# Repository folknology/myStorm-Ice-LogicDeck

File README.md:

# Ice LogicDeck 
The very first myStorm [Tile](https://github.com/folknology/Tiles) based logic deck, designed around the combination of a powerful STM32 F7 microcontroller fused with a fully configurable Lattice Ice40Hx FPGA.
This forms a modular, heterogeneous embedded development system, it is very much WIP. We will add more documentation soon, you can follow the [live](https://www.twitch.tv/folknology) streaming [narrative](https://www.youtube.com/playlist?list=PLXS9jyX9czzqn4HU2mEmoEFxpgIv1Dvy7) as we develop it, you can follow the evolving [documentation](https://folknology.github.io/myStorm-Ice-LogicDeck/).

#### The 'Deck' based solution is formed by combining multiple [Tiles](https://github.com/folknology/Tiles) and the Ice Logic board carrier

#### Together these form an Ice LogicDeck solution

### Hardware, development, tooling and software
- [Hardware sources](https://github.com/folknology/myStorm-Ice-LogicDeck/tree/main/Hardware)
- [Firmware sources](https://github.com/folknology/BlackCrab)
- [Examples & board support](https://github.com/folknology/myStorm-Ice-LogicDeck/tree/main/HDL)
- [FPGA HDL/Synthesis, PNR, simulation and formal - Yosys OSS cad suite](https://github.com/YosysHQ/oss-cad-suite-build)

### Further information
- [Tiles](https://github.com/folknology/Tiles)
- [Documentation](https://folknology.github.io/myStorm-Ice-LogicDeck/)
- [Discuss LogicDecks on Discord](https://discord.gg/RCGcgbQNZK)

### OpenSource Design

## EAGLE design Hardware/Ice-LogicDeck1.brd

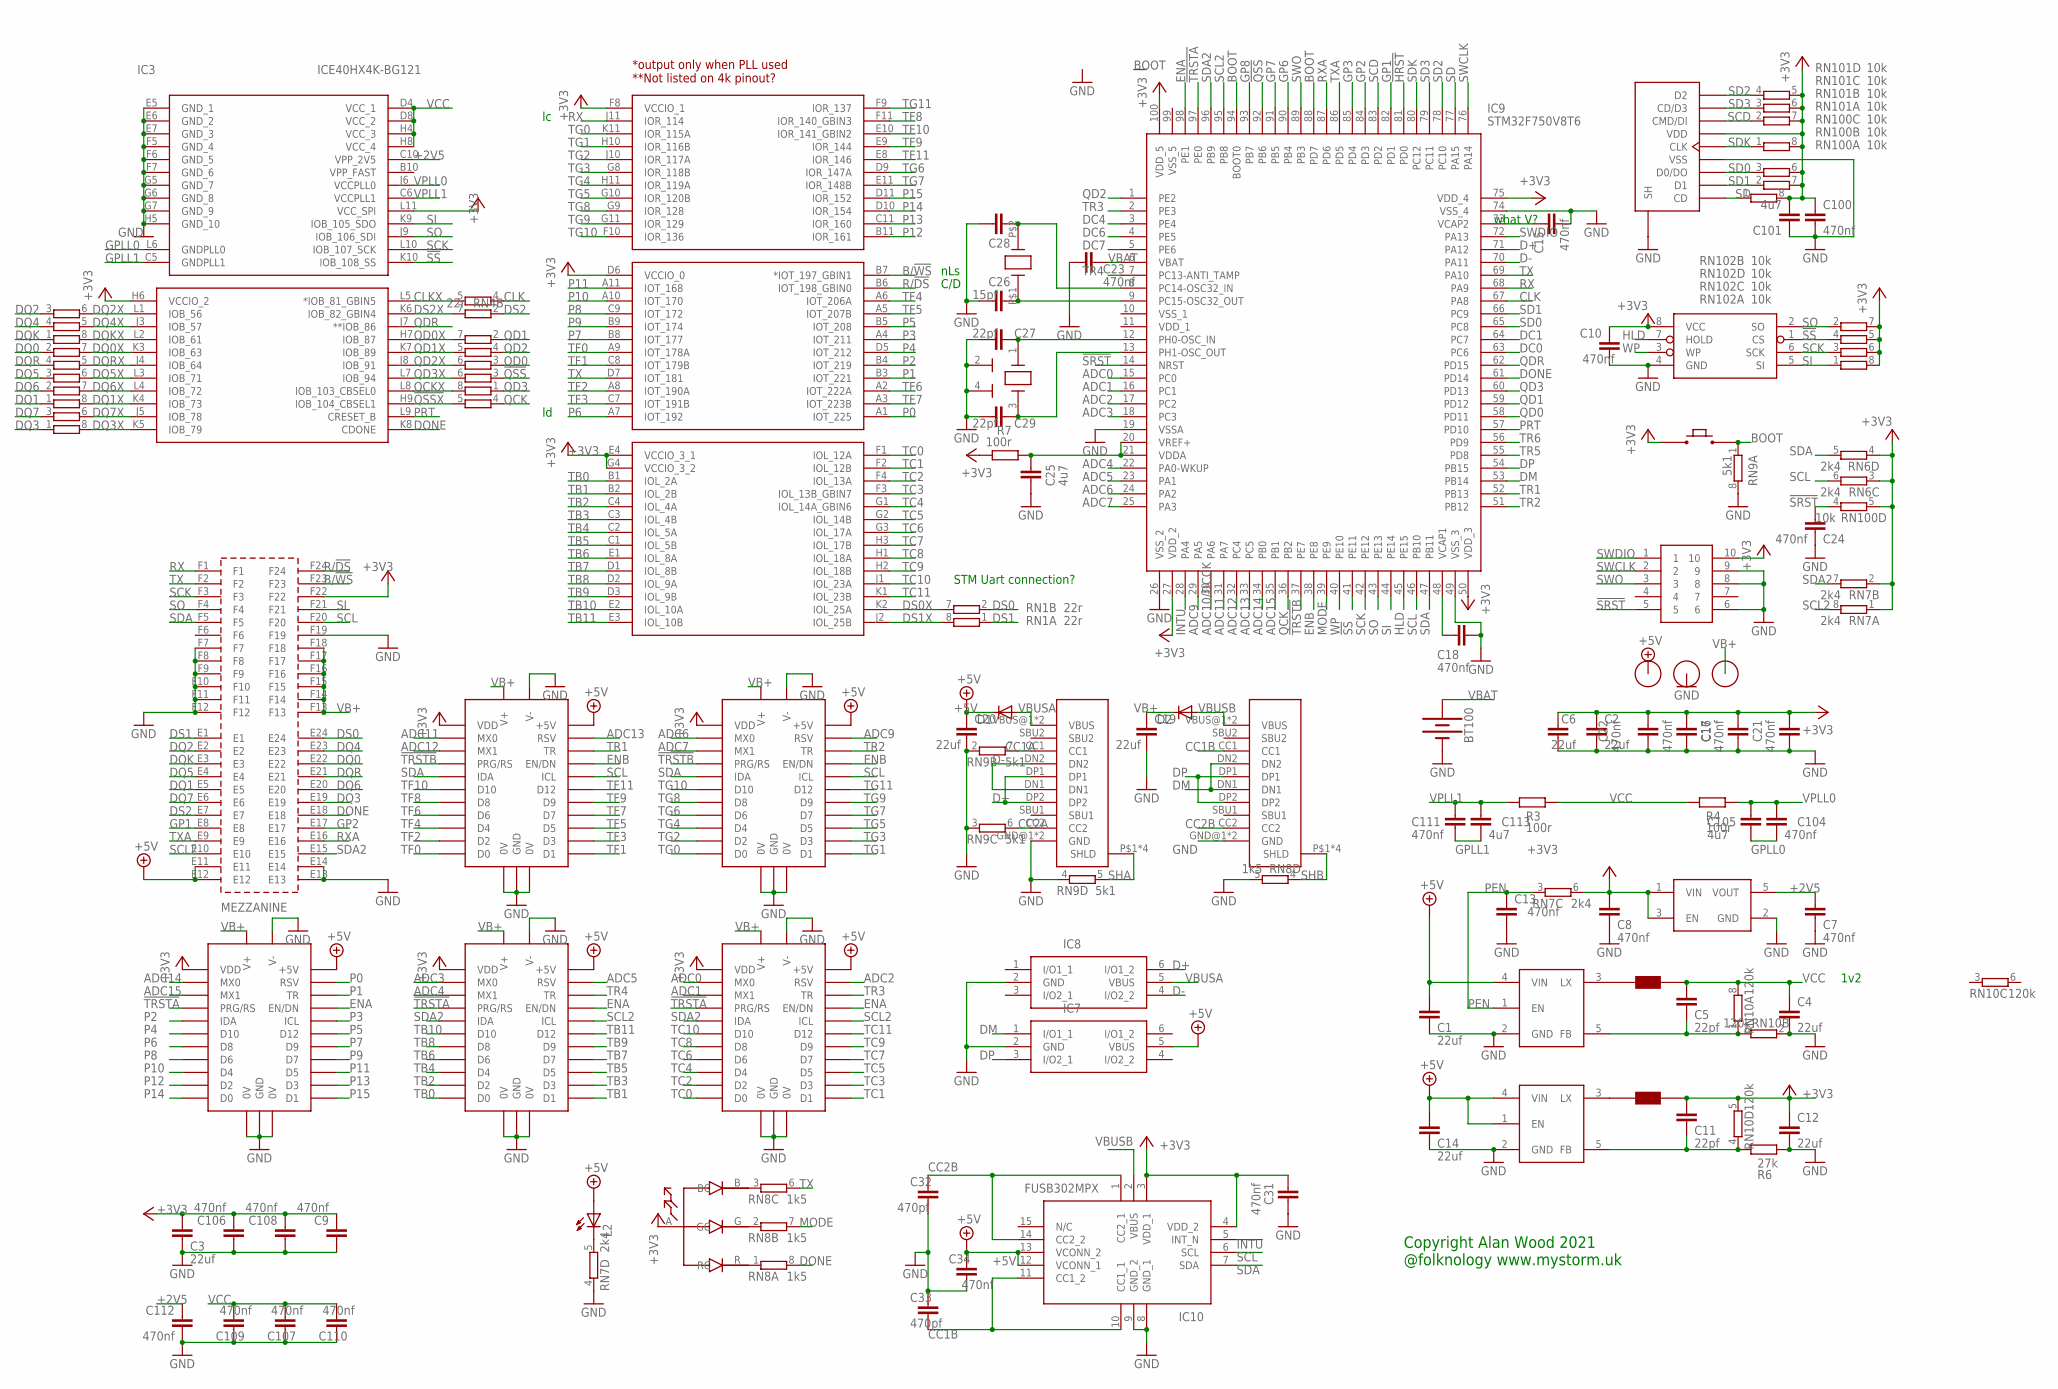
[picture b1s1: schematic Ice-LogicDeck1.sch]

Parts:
BT100: BATTERY-20MM_SMD; BATTCON_20MM
C1, C2, C3, C4, C6, C12, C14, C19, C20: 22uf; C0603
C5, C11, C27, C29: 22pf; C0402
C7, C8, C9, C10, C13, C15, C16, C17, C18, C21, C22, C23, C24, C31, C34, C100, C104, C106, C107, C108, C109, C110, C111, C112: 470nf; C0402
C25, C101, C105, C113: 4u7; C0402
C26, C28: 15pf; C0402
C32, C33: 470pf; C0402
CN1, CN2: USB-C-16; USB-C
CN3: 2X5-HEADER; 1.27-2X5-HEADER
D1, D2: DIODE-SOD123; SOD123
DFU: 4X3-RA-BUTTON
H1, H3, H4: HOLE2.5MM-LARGE; 2M5-LARGE
I1, I2: NRS4018; NRC4018
IC1, IC5: AP3429/A; TSOP-5/SOT23-5
IC2: NCP114; TSOP-5/SOT23-5
IC3: ICE40HX4K-BG121; BGA121C80P11X11_900X900X110
IC4: AT25SDF041A; SOIC-8-NARROW
IC7, IC8: USBLC6-2SC6; SOT95P280X145-6N
IC9: STM32F750V8T6; QFP50P1600X1600X160-100N
IC10: FUSB302MPX; QFN50P250X250X80-15N
L1: RGB_LED; RGB_LED_IMM
L2: LEDCHIPLED_0805; CHIPLED_0805
MEZZANINE: HYPER-TILECARRIER; HYPER-TILE
R3, R4, R7: 100r; R0402
R6: 27k; R0402
RN1, RN2, RN3, RN4, RN5: 22r; EXB38V
RN6, RN7: 2k4; EXB38V
RN8: 1k5; EXB38V
RN9: 5k1; EXB38V
RN10: 120k; EXB38V
RN100, RN101, RN102: 10k; EXB38V
SD100: TF-15X15; SDCARD
TILE1, TILE2, TILE3, TILE4, TILE5: UTILE_LPCARRIER_SMD_MALE_1.27; UTILE_LP
Y1: 12MZ; CRYSTAL-3.2X2.5
Y2: FC-135; FC135

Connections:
!HRST: IC9.81 (PD0)
!QSS: IC9.92 (PB6), RN4.3 (1)
!QSSX: IC3.H9 (IOB_104_CBSEL1), RN5.5 (2)
!SRST: C24.2, CN3.5, IC9.14 (NRST), RN100.4 (1)
!SS: IC3.K10 (IOB_108_SS), IC4.1 (CS), IC9.41 (PE11), RN102.4 (1)
!TRSTA: IC9.97 (PE0), TILE1.P$15 (PRG/RS), TILE2.P$15 (PRG/RS), TILE4.P$15 (PRG/RS)
!TRSTB: IC9.37 (PE7), TILE3.P$15 (PRG/RS), TILE5.P$15 (PRG/RS)
+2V5: C7.2, C112.1, IC2.5 (VOUT), IC3.C10 (VPP_2V5)
+3V3: C2.1, C3.2, C6.2, C8.2, C9.1, C10.1, C11.2, C12.1, C16.2, C17.2, C21.2, C22.2, C31.2, C100.1, C101.2, C106.1, C108.1, CN3.10, DFU.P$1, I2.P$2, IC2.1 (VIN), IC2.3 (EN), IC3.D6 (VCCIO_0), IC3.E4 (VCCIO_3_1), IC3.F8 (VCCIO_1), IC3.G4 (VCCIO_3_2), IC3.H6 (VCCIO_2), IC3.L11 (VCC_SPI), IC4.8 (VCC), IC9.27 (VDD_2), IC9.50 (VDD_3), IC9.75 (VDD_4), IC9.100 (VDD_5), IC10.3 (VDD_1), IC10.4 (VDD_2), L1.A (ANODE), MEZZANINE.F22, R7.2, RN6.3 (1), RN6.4 (1), RN7.1, RN7.2 (1), RN7.6 (2), RN10.5 (2), RN100.5 (2), RN100.6 (2), RN100.7 (2), RN100.8 (2), RN101.5 (2), RN101.6 (2), RN101.7 (2), RN101.8 (2), RN102.5 (2), RN102.6 (2), RN102.7 (2), RN102.8 (2), SD100.P$6 (VDD), TILE1.P$18 (VDD), TILE2.P$18 (VDD), TILE3.P$18 (VDD), TILE4.P$18 (VDD), TILE5.P$18 (VDD)
+5V: C1.2, C14.2, C20.1, C34.2, D1.C, H1.P$1, IC1.4 (VIN), IC5.1 (EN), IC5.4 (VIN), IC7.5 (VBUS), IC10.12 (VCONN_1), IC10.13 (VCONN_2), L2.A, MEZZANINE.E11, MEZZANINE.E12, TILE1.P$43 (+5V), TILE2.P$43 (+5V), TILE3.P$43 (+5V), TILE4.P$43 (+5V), TILE5.P$43 (+5V)
ADC0: IC9.15 (PC0), TILE4.P$17 (MX0)
ADC1: IC9.16 (PC1), TILE4.P$16 (MX1)
ADC2: IC9.17 (PC2), TILE4.P$42 (RSV)
ADC3: IC9.18 (PC3), TILE1.P$17 (MX0)
ADC4: IC9.22 (PA0-WKUP), TILE1.P$16 (MX1)
ADC5: IC9.23 (PA1), TILE1.P$42 (RSV)
ADC6: IC9.24 (PA2), TILE5.P$17 (MX0)
ADC7: IC9.25 (PA3), TILE5.P$16 (MX1)
ADC9: IC9.29 (PA5), TILE5.P$42 (RSV)
ADC10/DCCK: IC9.30 (PA6)
ADC11: IC9.31 (PA7), TILE3.P$17 (MX0)
ADC12: IC9.32 (PC4), TILE3.P$16 (MX1)
ADC13: IC9.33 (PC5), TILE3.P$42 (RSV)
ADC14: IC9.34 (PB0), TILE2.P$17 (MX0)
ADC15: IC9.35 (PB1), TILE2.P$16 (MX1)
B/!WS: IC3.B7 (*IOT_197_GBIN1), MEZZANINE.F23
BOOT: DFU.P$2, IC9.88 (PD7), IC9.94 (BOOT0), RN9.1
CC1A: CN1.CC1, RN9.7 (2)
CC1B: C33.1, CN2.CC1, IC10.10 (CC1_1), IC10.11 (CC1_2)
CC2A: CN1.CC2, RN9.6 (2)
CC2B: C32.2, CN2.CC2, IC10.1 (CC2_1), IC10.14 (CC2_2)
CLK: IC9.67 (PA8), RN3.4 (1)
CLKX: IC3.L5 (*IOB_81_GBIN5), RN3.5 (2)
D+: CN1.DP1, CN1.DP2, IC8.6 (I/O1_2), IC9.71 (PA12)
D-: CN1.DN1, CN1.DN2, IC8.4 (I/O2_2), IC9.70 (PA11)
DC0: IC9.63 (PC6)
DC1: IC9.64 (PC7)
DC4: IC9.3 (PE4)
DC6: IC9.4 (PE5)
DC7: IC9.5 (PE6)
DM: CN2.DN1, CN2.DN2, IC7.1 (I/O1_1), IC9.53 (PB14)
DONE: IC3.K8 (CDONE), IC9.61 (PD14), MEZZANINE.E18, RN8.8 (2)
DP: CN2.DP1, CN2.DP2, IC7.3 (I/O2_1), IC9.54 (PB15)
DQ0: MEZZANINE.E22, RN2.2 (1)
DQ0X: IC3.K3 (IOB_63), RN2.7 (2)
DQ1: MEZZANINE.E5, RN3.1
DQ1X: IC3.K4 (IOB_73), RN3.8 (2)
DQ2: MEZZANINE.E2, RN1.3 (1)
DQ2X: IC3.L1 (IOB_56), RN1.6 (2)
DQ3: MEZZANINE.E19, RN4.1
DQ3X: IC3.K5 (IOB_79), RN4.8 (2)
DQ4: MEZZANINE.E23, RN1.4 (1)
DQ4X: IC3.J3 (IOB_57), RN1.5 (2)
DQ5: MEZZANINE.E4, RN2.3 (1)
DQ5X: IC3.L3 (IOB_71), RN2.6 (2)
DQ6: MEZZANINE.E20, RN3.2 (1)
DQ6X: IC3.L4 (IOB_72), RN3.7 (2)
DQ7: MEZZANINE.E6, RN3.3 (1)
DQ7X: IC3.J5 (IOB_78), RN3.6 (2)
DQK: MEZZANINE.E3, RN2.1
DQKX: IC3.L2 (IOB_61), RN2.8 (2)
DQR: MEZZANINE.E21, RN2.4 (1)
DQRX: IC3.J4 (IOB_64), RN2.5 (2)
DS0: MEZZANINE.E24, RN1.2 (1)
DS0X: IC3.K2 (IOL_25A), RN1.7 (2)
DS1: MEZZANINE.E1, RN1.1
DS1X: IC3.J2 (IOL_25B), RN1.8 (2)
DS2: MEZZANINE.E7, RN4.2 (1)
DS2X: IC3.K6 (IOB_82_GBIN4), RN4.7 (2)
ENA: IC9.98 (PE1), TILE1.P$40 (EN/DN), TILE2.P$40 (EN/DN), TILE4.P$40 (EN/DN)
ENB: IC9.38 (PE8), TILE3.P$40 (EN/DN), TILE5.P$40 (EN/DN)
GND: BT100.2 (-), C1.1, C2.2, C3.1, C4.2, C6.1, C7.1, C8.1, C9.2, C10.2, C12.2, C13.2, C14.1, C15.2, C16.1, C17.1, C18.1, C19.2, C20.2, C21.1, C22.1, C23.2, C24.1, C25.2, C26.1, C27.1, C28.1, C29.1, C31.1, C32.1, C33.2, C34.1, C100.2, C101.1, C106.2, C107.1, C108.2, C109.1, C110.1, C112.2, CN1.GND@1 (GND), CN1.GND@2 (GND), CN2.GND@1 (GND), CN2.GND@2 (GND), CN3.6, CN3.8, CN3.9, H3.P$1, IC1.2 (GND), IC2.2 (GND), IC3.E5 (GND_1), IC3.E6 (GND_2), IC3.E7 (GND_3), IC3.F5 (GND_4), IC3.F6 (GND_5), IC3.F7 (GND_6), IC3.G5 (GND_7), IC3.G6 (GND_8), IC3.G7 (GND_9), IC3.H5 (GND_10), IC4.4 (GND), IC5.2 (GND), IC7.2 (GND), IC8.2 (GND), IC9.19 (VSSA), IC9.26 (VSS_2), IC9.49 (VSS_3), IC9.74 (VSS_4), IC10.8 (GND_1), IC10.9 (GND_2), MEZZANINE.E13, MEZZANINE.E14, MEZZANINE.F7, MEZZANINE.F8, MEZZANINE.F9, MEZZANINE.F10, MEZZANINE.F11, MEZZANINE.F12, MEZZANINE.F19, R6.2, RN7.4 (1), RN8.5 (2), RN9.2 (1), RN9.3 (1), RN9.4 (1), RN9.8 (2), RN10.2 (1), SD100.P$4 (VSS), SD100.P$10 (SH), SD100.P$11 (SH), SD100.P$12 (SH), SD100.P$13 (SH), TILE1.0V@1 (0V), TILE1.0V@2 (0V), TILE1.P$1 (V-), TILE1.P$2 (V-), TILE1.P$3 (V-), TILE1.P$4 (V-), TILE1.P$5 (V-), TILE1.P$6 (V-), TILE1.P$7 (GND), TILE1.P$26 (V-), TILE1.P$27 (V-), TILE1.P$28 (V-), TILE1.P$29 (V-), TILE1.P$30 (V-), TILE1.P$31 (V-), TILE1.P$32 (GND), TILE2.0V@1 (0V), TILE2.0V@2 (0V), TILE2.P$1 (V-), TILE2.P$2 (V-), TILE2.P$3 (V-), TILE2.P$4 (V-), TILE2.P$5 (V-), TILE2.P$6 (V-), TILE2.P$7 (GND), TILE2.P$26 (V-), TILE2.P$27 (V-), TILE2.P$28 (V-), TILE2.P$29 (V-), TILE2.P$30 (V-), TILE2.P$31 (V-), TILE2.P$32 (GND), TILE3.0V@1 (0V), TILE3.0V@2 (0V), TILE3.P$1 (V-), TILE3.P$2 (V-), TILE3.P$3 (V-), TILE3.P$4 (V-), TILE3.P$5 (V-), TILE3.P$6 (V-), TILE3.P$7 (GND), TILE3.P$26 (V-), TILE3.P$27 (V-), TILE3.P$28 (V-), TILE3.P$29 (V-), TILE3.P$30 (V-), TILE3.P$31 (V-), TILE3.P$32 (GND), TILE4.0V@1 (0V), TILE4.0V@2 (0V), TILE4.P$1 (V-), TILE4.P$2 (V-), TILE4.P$3 (V-), TILE4.P$4 (V-), TILE4.P$5 (V-), TILE4.P$6 (V-), TILE4.P$7 (GND), TILE4.P$26 (V-), TILE4.P$27 (V-), TILE4.P$28 (V-), TILE4.P$29 (V-), TILE4.P$30 (V-), TILE4.P$31 (V-), TILE4.P$32 (GND), TILE5.0V@1 (0V), TILE5.0V@2 (0V), TILE5.P$1 (V-), TILE5.P$2 (V-), TILE5.P$3 (V-), TILE5.P$4 (V-), TILE5.P$5 (V-), TILE5.P$6 (V-), TILE5.P$7 (GND), TILE5.P$26 (V-), TILE5.P$27 (V-), TILE5.P$28 (V-), TILE5.P$29 (V-), TILE5.P$30 (V-), TILE5.P$31 (V-), TILE5.P$32 (GND), Y1.2 (GND), Y1.4 (GND)
GP1: IC9.82 (PD1), MEZZANINE.E8
GP2: IC9.84 (PD3), MEZZANINE.E17
GP3: IC9.85 (PD4)
GP6: IC9.90 (PB4)
GP7: IC9.91 (PB5)
GP8: IC9.93 (PB7)
GPLL0: C104.1, C105.1, IC3.L6 (GNDPLL0)
GPLL1: C111.1, C113.1, IC3.C5 (GNDPLL1)
HLD: IC4.7 (HOLD), IC9.45 (PE15)
INTU: IC9.28 (PA4), IC10.5 (INT_N)
MODE: IC9.39 (PE9), RN8.7 (2)
unnamed: L2.C, RN7.5 (2)
unnamed: L1.G (GC), RN8.2 (1)
unnamed: L1.R (RC), RN8.1
unnamed: L1.B (BC), RN8.3 (1)
unnamed: C29.2, IC9.13 (PH1-OSC_OUT), Y1.3 (X2)
unnamed: C27.2, IC9.12 (PH0-OSC_IN), Y1.1 (X1)
unnamed: C26.2, IC9.9 (PC15-OSC32_OUT), Y2.P$1 (X1)
unnamed: C28.2, IC9.8 (PC14-OSC32_IN), Y2.P$2 (X2)
unnamed: C15.1, IC9.73 (VCAP2)
unnamed: C11.1, IC5.5 (FB), R6.1, RN10.4 (1)
unnamed: I2.P$1, IC5.3 (LX)
unnamed: C18.2, IC9.48 (VCAP1)
unnamed: C25.1, IC9.20 (VREF+), IC9.21 (VDDA), R7.1
unnamed: C5.1, IC1.5 (FB), RN10.1, RN10.7 (2)
unnamed: I1.P$1, IC1.3 (LX)
P0: IC3.A1 (IOT_225), TILE2.P$42 (RSV)
P1: IC3.B3 (IOT_221), TILE2.P$41 (TR)
P2: IC3.B4 (IOT_219), TILE2.P$14 (IDA)
P3: IC3.A4 (IOT_211), TILE2.P$39 (ICL)
P4: IC3.D5 (IOT_212), TILE2.P$13 (D10)
P5: IC3.B5 (IOT_208), TILE2.P$38 (D12)
P6: IC3.A7 (IOT_192), TILE2.P$12 (D8)
P7: IC3.B8 (IOT_177), TILE2.P$37 (D9)
P8: IC3.C9 (IOT_172), TILE2.P$11 (D6)
P9: IC3.B9 (IOT_174), TILE2.P$36 (D7)
P10: IC3.A10 (IOT_170), TILE2.P$10 (D4)
P11: IC3.A11 (IOT_168), TILE2.P$35 (D5)
P12: IC3.B11 (IOR_161), TILE2.P$9 (D2)
P13: IC3.C11 (IOR_160), TILE2.P$34 (D3)
P14: IC3.D10 (IOR_154), TILE2.P$8 (D0)
P15: IC3.D11 (IOR_152), TILE2.P$33 (D1)
PEN: C13.1, IC1.1 (EN), RN7.3 (1)
PRT: IC3.L9 (CRESET_B), IC9.57 (PD10)
QCK: IC9.36 (PB2), RN5.4 (1)
QCKX: IC3.L8 (IOB_103_CBSEL0), RN5.8 (2)
QD0: IC9.58 (PD11), RN5.3 (1)
QD0X: IC3.H7 (IOB_87), RN5.7 (2)
QD1: IC9.59 (PD12), RN5.2 (1)
QD1X: IC3.K7 (IOB_89), RN4.5 (2)
QD2: IC9.1 (PE2), RN4.4 (1)
QD2X: IC3.J8 (IOB_91), RN5.6 (2)
QD3: IC9.60 (PD13), RN5.1
QD3X: IC3.L7 (IOB_94), RN4.6 (2)
QDR: IC3.J7 (**IOB_86), IC9.62 (PD15)
R/!DS: IC3.B6 (IOT_198_GBIN0), MEZZANINE.F24
RX: IC3.J11 (IOR_114), IC9.68 (PA9), MEZZANINE.F1
RXA: IC9.87 (PD6), MEZZANINE.E16
SCD: IC9.83 (PD2), RN101.2 (1), SD100.P$7 (CMD/DI)
SCK: IC3.L10 (IOB_107_SCK), IC4.6 (SCK), IC9.42 (PE12), MEZZANINE.F3, RN102.3 (1)
SCL: IC9.46 (PB10), IC10.6 (SCL), MEZZANINE.F20, RN6.6 (2), TILE3.P$39 (ICL), TILE5.P$39 (ICL)
SCL2: IC9.95 (PB8), MEZZANINE.E10, RN7.8 (2), TILE1.P$39 (ICL), TILE4.P$39 (ICL)
SD: IC9.77 (PA15), RN100.1, SD100.P$1 (CD)
SD0: IC9.65 (PC8), RN100.3 (1), SD100.P$3 (D0/DO)
SD1: IC9.66 (PC9), RN100.2 (1), SD100.P$2 (D1)
SD2: IC9.78 (PC10), RN101.4 (1), SD100.P$9 (D2)
SD3: IC9.79 (PC11), RN101.3 (1), SD100.P$8 (CD/D3)
SDA: IC9.47 (PB11), IC10.7 (SDA), MEZZANINE.F5, RN6.5 (2), TILE3.P$14 (IDA), TILE5.P$14 (IDA)
SDA2: IC9.96 (PB9), MEZZANINE.E15, RN7.7 (2), TILE1.P$14 (IDA), TILE4.P$14 (IDA)
SDK: IC9.80 (PC12), RN101.1, SD100.P$5 (CLK)
SHA: CN1.P$1 (SHLD), CN1.P$2 (SHLD), CN1.P$3 (SHLD), CN1.P$4 (SHLD), RN9.5 (2)
SHB: CN2.P$1 (SHLD), CN2.P$2 (SHLD), CN2.P$3 (SHLD), CN2.P$4 (SHLD), RN8.4 (1)
SI: IC3.K9 (IOB_105_SDO), IC4.5 (SI), IC9.44 (PE14), MEZZANINE.F21, RN102.1
SO: IC3.J9 (IOB_106_SDI), IC4.2 (SO), IC9.43 (PE13), MEZZANINE.F4, RN102.2 (1)
SWCLK: CN3.2, IC9.76 (PA14)
SWDIO: CN3.1, IC9.72 (PA13)
SWO: CN3.3, IC9.89 (PB3)
TB0: IC3.B1 (IOL_2A), TILE1.P$8 (D0)
TB1: IC3.B2 (IOL_2B), TILE1.P$33 (D1)
TB2: IC3.C4 (IOL_4A), TILE1.P$9 (D2)
TB3: IC3.C3 (IOL_4B), TILE1.P$34 (D3)
TB4: IC3.C2 (IOL_5A), TILE1.P$10 (D4)
TB5: IC3.C1 (IOL_5B), TILE1.P$35 (D5)
TB6: IC3.E1 (IOL_8A), TILE1.P$11 (D6)
TB7: IC3.D1 (IOL_8B), TILE1.P$36 (D7)
TB8: IC3.D2 (IOL_9A), TILE1.P$12 (D8)
TB9: IC3.D3 (IOL_9B), TILE1.P$37 (D9)
TB10: IC3.E2 (IOL_10A), TILE1.P$13 (D10)
TB11: IC3.E3 (IOL_10B), TILE1.P$38 (D12)
TC0: IC3.F1 (IOL_12A), TILE4.P$8 (D0)
TC1: IC3.F2 (IOL_12B), TILE4.P$33 (D1)
TC2: IC3.F4 (IOL_13A), TILE4.P$9 (D2)
TC3: IC3.F3 (IOL_13B_GBIN7), TILE4.P$34 (D3)
TC4: IC3.G1 (IOL_14A_GBIN6), TILE4.P$10 (D4)
TC5: IC3.G2 (IOL_14B), TILE4.P$35 (D5)
TC6: IC3.G3 (IOL_17A), TILE4.P$11 (D6)
TC7: IC3.H3 (IOL_17B), TILE4.P$36 (D7)
TC8: IC3.H1 (IOL_18A), TILE4.P$12 (D8)
TC9: IC3.H2 (IOL_18B), TILE4.P$37 (D9)
TC10: IC3.J1 (IOL_23A), TILE4.P$13 (D10)
TC11: IC3.K1 (IOL_23B), TILE4.P$38 (D12)
TF0: IC3.A9 (IOT_178A), TILE3.P$8 (D0)
TF1: IC3.C8 (IOT_179B), TILE3.P$33 (D1)
TF2: IC3.A8 (IOT_190A), TILE3.P$9 (D2)
TF3: IC3.C7 (IOT_191B), TILE3.P$34 (D3)
TF4: IC3.A6 (IOT_206A), TILE3.P$10 (D4)
TF5: IC3.A5 (IOT_207B), TILE3.P$35 (D5)
TF6: IC3.A2 (IOT_222A), TILE3.P$11 (D6)
TF7: IC3.A3 (IOT_223B), TILE3.P$36 (D7)
TF8: IC3.F11 (IOR_140_GBIN3), TILE3.P$12 (D8)
TF9: IC3.E9 (IOR_144), TILE3.P$37 (D9)
TF10: IC3.E10 (IOR_141_GBIN2), TILE3.P$13 (D10)
TF11: IC3.E8 (IOR_146), TILE3.P$38 (D12)
TG0: IC3.K11 (IOR_115A), TILE5.P$8 (D0)
TG1: IC3.H10 (IOR_116B), TILE5.P$33 (D1)
TG2: IC3.J10 (IOR_117A), TILE5.P$9 (D2)
TG3: IC3.G8 (IOR_118B), TILE5.P$34 (D3)
TG4: IC3.H11 (IOR_119A), TILE5.P$10 (D4)
TG5: IC3.G10 (IOR_120B), TILE5.P$35 (D5)
TG6: IC3.D9 (IOR_147A), TILE5.P$11 (D6)
TG7: IC3.E11 (IOR_148B), TILE5.P$36 (D7)
TG8: IC3.G9 (IOR_128), TILE5.P$12 (D8)
TG9: IC3.G11 (IOR_129), TILE5.P$37 (D9)
TG10: IC3.F10 (IOR_136), TILE5.P$13 (D10)
TG11: IC3.F9 (IOR_137), TILE5.P$38 (D12)
TR1: IC9.52 (PB13), TILE3.P$41 (TR)
TR2: IC9.51 (PB12), TILE5.P$41 (TR)
TR3: IC9.2 (PE3), TILE4.P$41 (TR)
TR4: IC9.7 (PC13-ANTI_TAMP), TILE1.P$41 (TR)
TR5: IC9.55 (PD8)
TR6: IC9.56 (PD9)
TX: IC3.D7 (IOT_181), IC9.69 (PA10), MEZZANINE.F2, RN8.6 (2)
TXA: IC9.86 (PD5), MEZZANINE.E9
VB+: C19.1, D2.C, H4.P$1, MEZZANINE.F13, MEZZANINE.F14, MEZZANINE.F15, MEZZANINE.F16, MEZZANINE.F17, MEZZANINE.F18, TILE1.P$20 (V+), TILE1.P$21 (V+), TILE1.P$22 (V+), TILE1.P$23 (V+), TILE1.P$24 (V+), TILE1.P$25 (V+), TILE1.P$45 (V+), TILE1.P$46 (V+), TILE1.P$47 (V+), TILE1.P$48 (V+), TILE1.P$49 (V+), TILE1.P$50 (V+), TILE2.P$20 (V+), TILE2.P$21 (V+), TILE2.P$22 (V+), TILE2.P$23 (V+), TILE2.P$24 (V+), TILE2.P$25 (V+), TILE2.P$45 (V+), TILE2.P$46 (V+), TILE2.P$47 (V+), TILE2.P$48 (V+), TILE2.P$49 (V+), TILE2.P$50 (V+), TILE3.P$20 (V+), TILE3.P$21 (V+), TILE3.P$22 (V+), TILE3.P$23 (V+), TILE3.P$24 (V+), TILE3.P$25 (V+), TILE3.P$45 (V+), TILE3.P$46 (V+), TILE3.P$47 (V+), TILE3.P$48 (V+), TILE3.P$49 (V+), TILE3.P$50 (V+), TILE4.P$20 (V+), TILE4.P$21 (V+), TILE4.P$22 (V+), TILE4.P$23 (V+), TILE4.P$24 (V+), TILE4.P$25 (V+), TILE4.P$45 (V+), TILE4.P$46 (V+), TILE4.P$47 (V+), TILE4.P$48 (V+), TILE4.P$49 (V+), TILE4.P$50 (V+), TILE5.P$20 (V+), TILE5.P$21 (V+), TILE5.P$22 (V+), TILE5.P$23 (V+), TILE5.P$24 (V+), TILE5.P$25 (V+), TILE5.P$45 (V+), TILE5.P$46 (V+), TILE5.P$47 (V+), TILE5.P$48 (V+), TILE5.P$49 (V+), TILE5.P$50 (V+)
VBAT: BT100.1 (+), C23.1, IC9.6 (VBAT)
VBUSA: CN1.VBUS@1 (VBUS), CN1.VBUS@2 (VBUS), D1.A, IC8.5 (VBUS)
VBUSB: CN2.VBUS@1 (VBUS), CN2.VBUS@2 (VBUS), D2.A, IC10.2 (VBUS)
VCC: C4.1, C5.2, C107.2, C109.2, C110.2, I1.P$2, IC3.D4 (VCC_1), IC3.D8 (VCC_2), IC3.H4 (VCC_3), IC3.H8 (VCC_4), R3.1, R4.2, RN10.8 (2)
VPLL0: C104.2, C105.2, IC3.J6 (VCCPLL0), R4.1
VPLL1: C111.2, C113.2, IC3.C6 (VCCPLL1), R3.2
WP: IC4.3 (WP), IC9.40 (PE10)

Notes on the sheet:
Copyright Alan Wood 2021 @folknology www.mystorm.uk
1v2
nLs
C/D
STM Uart connection?
what V?

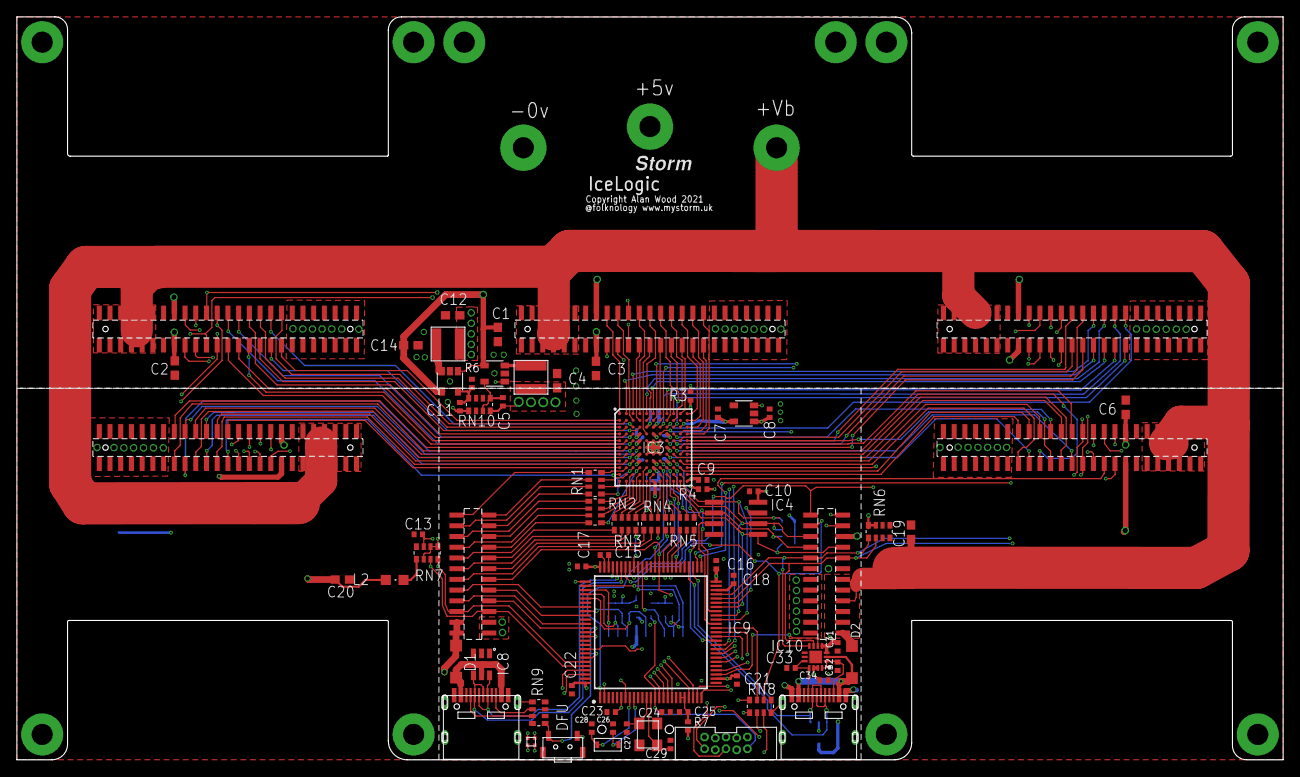
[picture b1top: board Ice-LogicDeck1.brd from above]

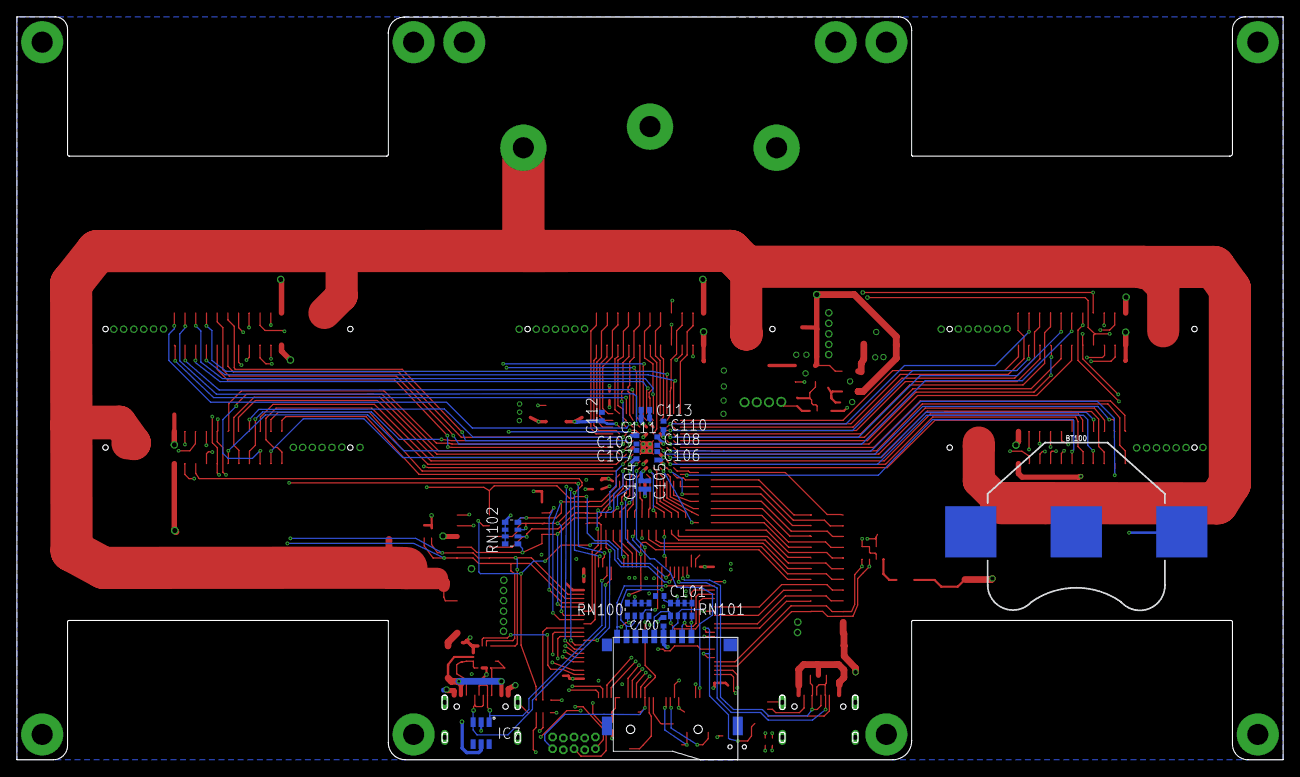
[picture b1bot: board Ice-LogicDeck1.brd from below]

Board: 4 copper layers, 150.0 x 88.0 mm, 94 parts (18 on the bottom side), 200 nets.

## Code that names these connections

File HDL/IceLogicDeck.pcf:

set_io clk L5

# Tile 1
set_io -nowarn tile1[0] B1
set_io -nowarn  tile1[1] B2
set_io -nowarn  tile1[2] C4
set_io -nowarn  tile1[3] C3
set_io -nowarn  tile1[4] C2
set_io -nowarn  tile1[5] C1
set_io -nowarn  tile1[6] E1
set_io -nowarn  tile1[7] D1
set_io -nowarn  tile1[8] D2
set_io -nowarn  tile1[9] D3
set_io -nowarn  tile1[10] E2
set_io -nowarn  tile1[11] E3

# Tile 2 (super tile)
set_io tile2[0] D10 # p14
set_io tile2[1] D11 # p15
set_io tile2[2] B11 # p12
set_io tile2[3] C11 # p13
set_io tile2[4] A10 # p10
set_io tile2[5] A11 # p11
set_io tile2[6] C9 # p9
set_io tile2[7] B9 # p8
set_io tile2[8] A7 # p7
set_io tile2[9] B8 # p6
set_io tile2[10] D5 # p5
set_io tile2[11] B5 # p4
set_io -nowarn  sda B4 # p3
set_io -nowarn  scl A4 # p2
set_io -nowarn  rsv A1 # p1
set_io -nowarn  tr B3 # p0


# Tile 3
set_io -nowarn  tile3[0] A9
set_io -nowarn  tile3[1] C8
set_io -nowarn  tile3[2] A8
set_io -nowarn  tile3[3] C7
set_io -nowarn  tile3[4] A6
set_io -nowarn  tile3[5] A5
set_io -nowarn  tile3[6] A2
set_io -nowarn  tile3[7] A3
set_io -nowarn  tile3[8] F11
set_io -nowarn  tile3[9] E9
set_io -nowarn  tile3[10] E10
set_io -nowarn  tile3[11] E8

# Tile 4
set_io -nowarn  tile4[0] F1
set_io -nowarn  tile4[1] F2
set_io -nowarn  tile4[2] F4
set_io -nowarn  tile4[3] F3
set_io -nowarn  tile4[4] G1
set_io -nowarn  tile4[5] G2
set_io -nowarn  tile4[6] G3
set_io -nowarn  tile4[7] H3
set_io -nowarn  tile4[8] H1
set_io -nowarn  tile4[9] H2
set_io -nowarn  tile4[10] J1
set_io -nowarn  tile4[11] K1

# Tile 5
set_io -nowarn  tile5[0] K11
set_io -nowarn  tile5[1] H10
set_io -nowarn  tile5[2] J10
set_io -nowarn  tile5[3] G8
set_io -nowarn  tile5[4] H11
set_io -nowarn  tile5[5] G10
set_io -nowarn  tile5[6] D9
set_io -nowarn  tile5[7] E11
set_io -nowarn  tile5[8] G9
set_io -nowarn  tile5[9] G11
set_io -nowarn  tile5[10] F10
set_io -nowarn  tile5[11] F9

# HyperRam
set_io -nowarn  dq[0] K3
set_io -nowarn  dq[1] K4
set_io -nowarn  dq[2] L1
set_io -nowarn  dq[3] K5
set_io -nowarn  dq[4] J3
set_io -nowarn  dq[5] L3
set_io -nowarn  dq[6] L4
set_io -nowarn  dq[7] J5
set_io -nowarn  dqk L2
set_io -nowarn  dqr J4
set_io -nowarn  ds0 K6

# QsPie
set_io -nowarn  qd[0] J8
set_io -nowarn  qd[1] H7
set_io -nowarn  qd[2] K7
set_io -nowarn  qd[3] L8
set_io -nowarn  qck H9
set_io -nowarn  qss L7
set_io -nowarn  qdr J7

# SPI
set_io -nowarn  si K9
set_io -nowarn  so J9
set_io -nowarn  sck L10
set_io -nowarn  ss L7

# Uart
set_io -nowarn  tx K2
set_io -nowarn  rx J2

# Mezzanine
set_io -nowarn  mt0 J11 # lc
set_io -nowarn  g_mt1 D7 # ld
set_io -nowarn  b_ws B7 # nls
set_io -nowarn  r_ds B6 # lc/d

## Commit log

2021-10-17 Edited readme
2021-10-17 Added more to readme
2021-10-17 Added initial versions of eagle cad files and pdf schematic
2021-10-17 Added schematic and layout previews
2021-10-17 Fixed readme image link again!
2021-10-17 Edited readme added discord link to #LogicDeck
2021-10-17 Added readme tile link
2021-10-17 Juggled some pins to improve IO frm @tnt suggestion
2021-10-18 Added series resistors for fast data lines and a cs jumper to alloy hyperflash to be swapped by 2nd hyperram
2021-10-18 Cleaned up schematic and updated previews
2021-10-18 REarranged TG/F pinouts for pait matches updated schematic and previews
2021-10-19 Improved the routing a little
2021-12-22 Added PCF and Amaranth Board files
2021-12-22 Changed from generic led array naming to tile array naming
2021-12-22 Added Amaranth board file for Ice LogicDeck along with simple proto led test
2021-12-31 Added Seven segment tile test and new mezzanine A hyperbus pinout
2022-01-01 Made the 7 seg resource creation more pythonic and slightly less verbose
2022-01-01 Refactored the resources to be tile centric for Seven segment tile example
2022-01-06 Added Seven Segment and AV tiles along with mdbook based LabNotes
2022-01-06 Temporarily added book by disabling the git ignore until I cal work out the continuous Integration required
2022-01-13 Added blinky and a experimental docs dir
2022-01-27 Updated Docs
2022-01-27 Updated Readme headings
2022-01-27 Updated hardware Docs and corrected a few things
2022-01-27 Added missing images
2022-01-27 Corrected Yosy cad suite links
2022-01-27 Corrected Yosys cad suite links
2022-01-27 removed verilator link changed header styles
2022-01-27 Updated Images for layout and schematic
2022-01-27 Updated schematic
2022-01-27 Updated readme headers
2022-02-05 Updated images for readme
2022-05-04 Updated Sevenseg and Tester tiles for IceLogicBus + BiNxt
2022-05-11 Updated verilog blink example for ILB, convereted make file to NextPnr
2022-05-23 Updated tile examples for changes on final tile versions
2022-05-25 Refactored things a little
2022-05-25 Added pll.py
2022-06-29 added trail example for blade1

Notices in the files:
parts and their libraries:
SparkFun-Batteries: Licensing: Creative Commons ShareAlike 4.0 International - https://creativecommons.org/licenses/by-sa/4.0
